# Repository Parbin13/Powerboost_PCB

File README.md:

# PCB Power Booster and Controller

This repository contains the design files for a custom PCB created to boost 5V power to 12V and control various components such as solenoids, servos, and ultrasonic sensors. The PCB was designed using KiCAD and includes schematic and layout files, as well as 3D renderings of the final board.

## Project Overview
This PCB is designed for a project that involves controlling components while boosting a 5V input power supply to 12V for powering solenoids and other devices. It includes the following features:
- **Boost Converter**: Steps up 5V to 12V for high-power components.
- **Solenoid Driver**: Controls solenoids using the boosted 12V power.
- **Ultrasonic Sensor Interface**: Allows connection and control of ultrasonic sensors.
- **Servo Motor Controllers**: Provides control for multiple servos.

The PCB was designed using KiCAD, an open-source electronic design automation (EDA) tool.

### PCB Features
- **Power Boost Circuit**: Converts 5V input to 12V using a boost converter, providing sufficient power for solenoids and other high-power components.
- **Microcontroller Interface**: Designed to work with a microcontroller for controlling external components.
- **Component Footprints**: Includes headers for connecting solenoids, ultrasonic sensors, and servos.
- **Power Supply and Regulation**: Manages power distribution and voltage regulation for all components.

## Project Files
- **Schematic File (.sch)**: Contains the electronic circuit schematic, including the boost converter and control components.
- **Layout File (.kicad_pcb)**: Contains the PCB layout, routing, and component placement.
- **3D Model**: Visual representation of the PCB design to assist in assembly.

## Setup Instructions
To view and modify the PCB design:
1. Install **KiCAD** from [here](https://kicad.org/).
2. Clone the repository:
   ```bash
   git clone https://github.com/Parbin13/PCB_PowerBooster_Controller.git

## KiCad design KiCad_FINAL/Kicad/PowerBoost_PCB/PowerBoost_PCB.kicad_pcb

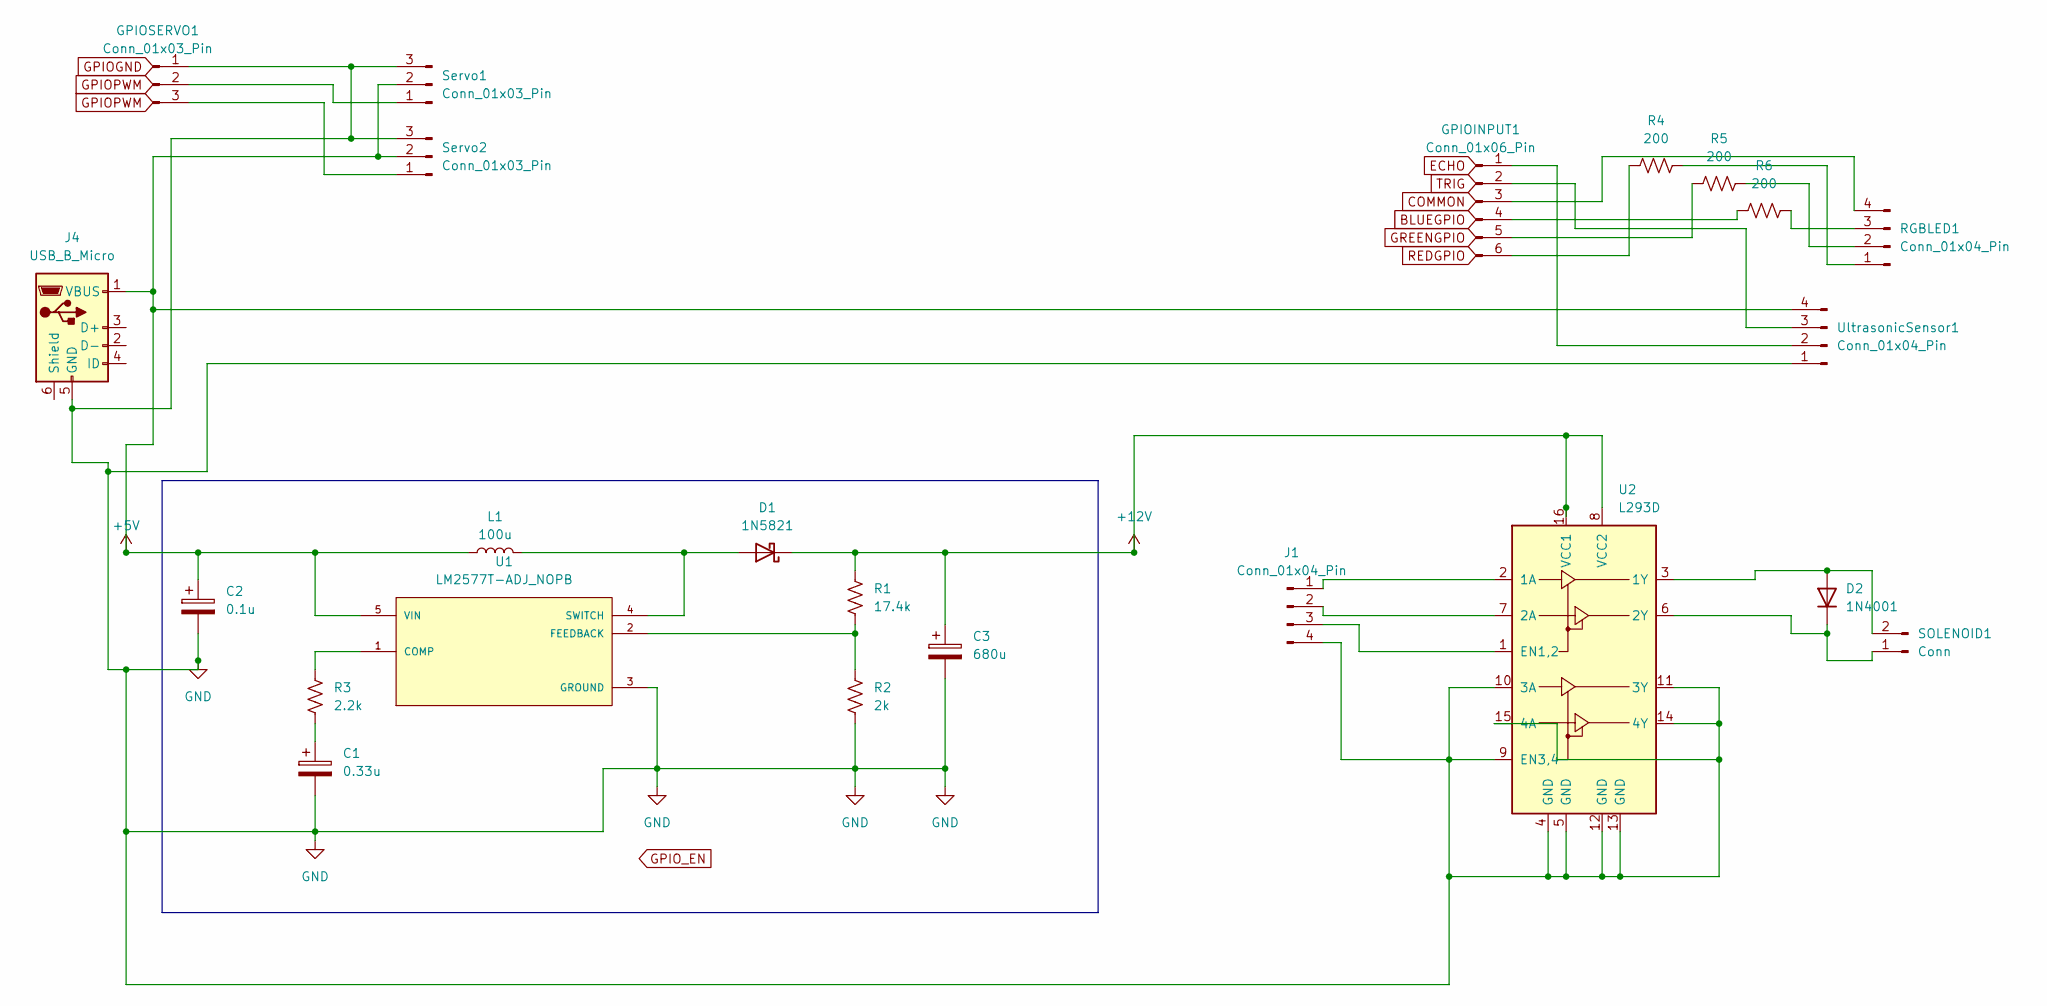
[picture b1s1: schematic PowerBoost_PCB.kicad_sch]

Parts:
C1: 0.33u; CP_Radial_D5.0mm_P2.50mm
C2: 0.1u; CP_Radial_D5.0mm_P2.50mm
C3: 680u; CP_Radial_D10.0mm_P5.00mm
D1: 1N5821; D_DO-201AD_P15.24mm_Horizontal
D2: 1N4001; D_DO-41_SOD81_P10.16mm_Horizontal
GPIOINPUT1: Conn_01x06_Pin
GPIOSERVO1: Conn_01x03_Pin
J1: Conn_01x04_Pin; JST_EH_B4B-EH-A_1x04_P2.50mm_Vertical
J4: USB_B_Micro
L1: 100u; L_Radial_D8.7mm_P5.00mm_Fastron_07HCP
R1: 17.4k; R_Axial_DIN0204_L3.6mm_D1.6mm_P7.62mm_Horizontal
R2: 2k; R_Axial_DIN0204_L3.6mm_D1.6mm_P7.62mm_Horizontal
R3: 2.2k; R_Axial_DIN0204_L3.6mm_D1.6mm_P7.62mm_Horizontal
R4, R5, R6: 200; R_Axial_DIN0204_L3.6mm_D1.6mm_P7.62mm_Horizontal
RGBLED1: Conn_01x04_Pin
SOLENOID1: Conn; JST_EH_B2B-EH-A_1x02_P2.50mm_Vertical
Servo1, Servo2: Conn_01x03_Pin
U1: LM2577T-ADJ_NOPB; VREG_LM2577T-ADJ_NOPB; PARTREV D
U2: L293D; DIP-16_W7.62mm
UltrasonicSensor1: Conn_01x04_Pin

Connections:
+5V: C2.1, J4.1 (VBUS), L1.1, Servo1.2, Servo2.2, U1.5 (VIN), UltrasonicSensor1.4
+12V: C3.1, D1.1 (K), R1.1, U2.8 (VCC2), U2.16 (VCC1)
GND: C1.2, C2.2, C3.2, GPIOSERVO1.1, J1.4, J4.5 (GND), R2.2, Servo1.3, Servo2.3, U1.3 (GROUND), U2.4 (GND), U2.5 (GND), U2.9 (EN3,4), U2.10 (3A), U2.11 (3Y), U2.12 (GND), U2.13 (GND), U2.14 (4Y), U2.15 (4A), UltrasonicSensor1.1
unnamed: C1.1, R3.2
unnamed: D1.2 (A), L1.2, U1.4 (SWITCH)
unnamed: D2.2 (A), SOLENOID1.2, U2.3 (1Y)
unnamed: D2.1 (K), SOLENOID1.1, U2.6 (2Y)
unnamed: GPIOINPUT1.1, UltrasonicSensor1.2
unnamed: GPIOINPUT1.2, UltrasonicSensor1.3
unnamed: GPIOINPUT1.3, RGBLED1.4
unnamed: GPIOINPUT1.4, R6.1
unnamed: GPIOINPUT1.5, R5.2
unnamed: GPIOINPUT1.6, R4.1
unnamed: GPIOSERVO1.2, Servo1.1
unnamed: GPIOSERVO1.3, Servo2.1
unnamed: J1.1, U2.2 (1A)
unnamed: J1.2, U2.7 (2A)
unnamed: J1.3, U2.1 (EN1,2)
unnamed: R4.2, RGBLED1.1
unnamed: R5.1, RGBLED1.2
unnamed: R6.2, RGBLED1.3
unnamed: R3.1, U1.1 (COMP)
unnamed: R1.2, R2.1, U1.2 (FEEDBACK)

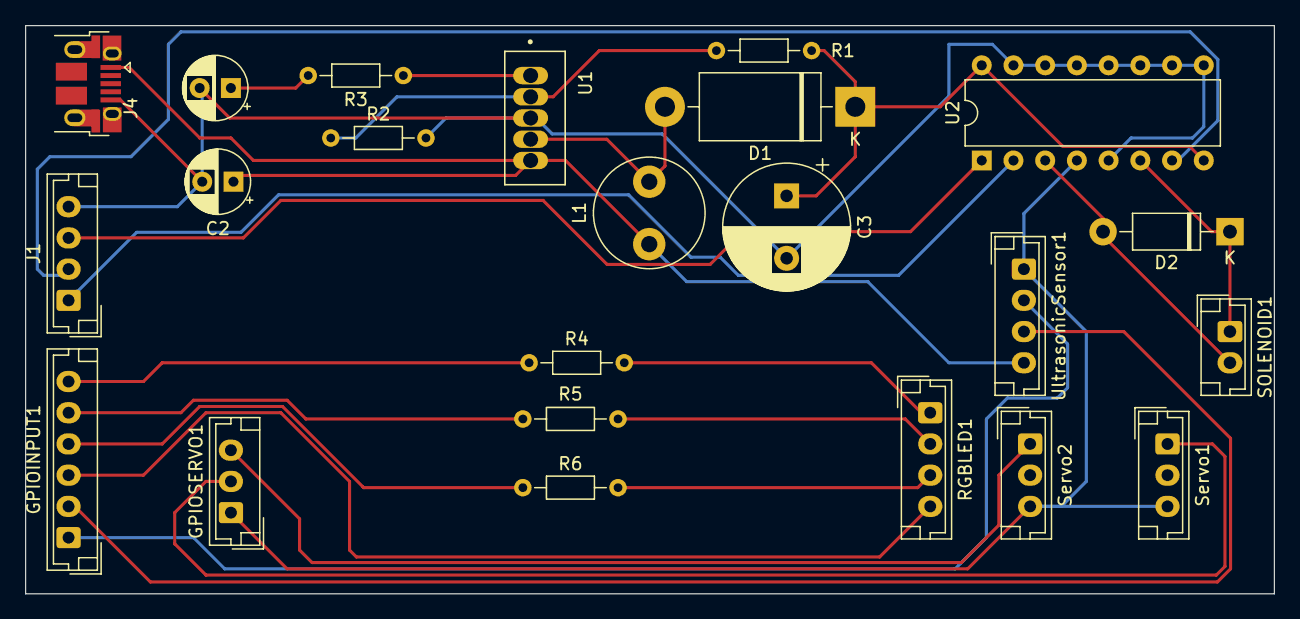
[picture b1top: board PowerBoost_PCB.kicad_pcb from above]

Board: 2 copper layers, 100.0 x 45.5 mm, 23 parts (0 on the bottom side), 23 nets.
